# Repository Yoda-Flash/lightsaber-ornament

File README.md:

# lightsaber-ornament
A lightsaber ornament made for Hack Club's Hacky Holidays!

At first, I wanted to make a Yoda ornament PCB, but I realized that it would only look good with green colored lights. Upon further thought, I realized that Lightsabers would look good in nearly any color, which made it perfect as an ornament. Hence, I decided to make this lightsaber ornament PCB, to bring joy to all Star Wars lovers during the holidays!

A simulation of it can be found here: https://wokwi.com/projects/421435412428006401

### 3D Views
#### Front

- 8 Neopixel LEDs, can be set to any color (currently Lightsaber Blue, RGB(46,103,248))
- Piano switch to turn the PCB on and off
- Charger for battery (Only use if the battery is rechargeable!!!)

#### Back

- 4 batteries, which must be CIR2032 form factors

### Schematic

- LEDs, Charger and regulator, Battery, ESP32

### PCB

*Everything made with KiCAD

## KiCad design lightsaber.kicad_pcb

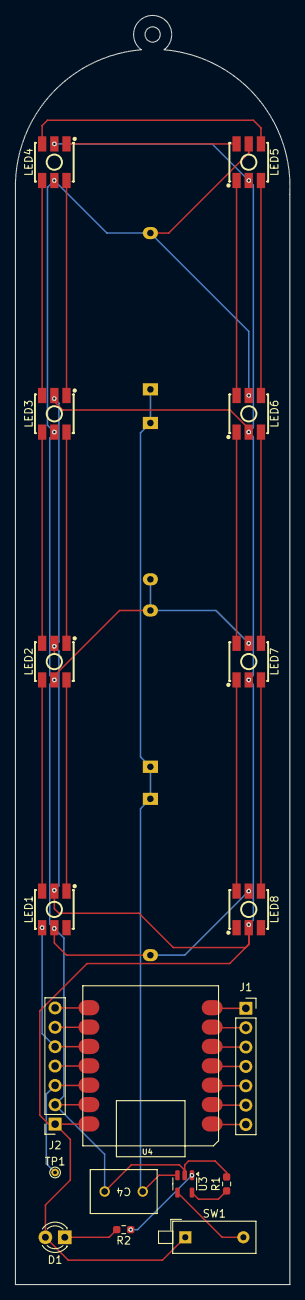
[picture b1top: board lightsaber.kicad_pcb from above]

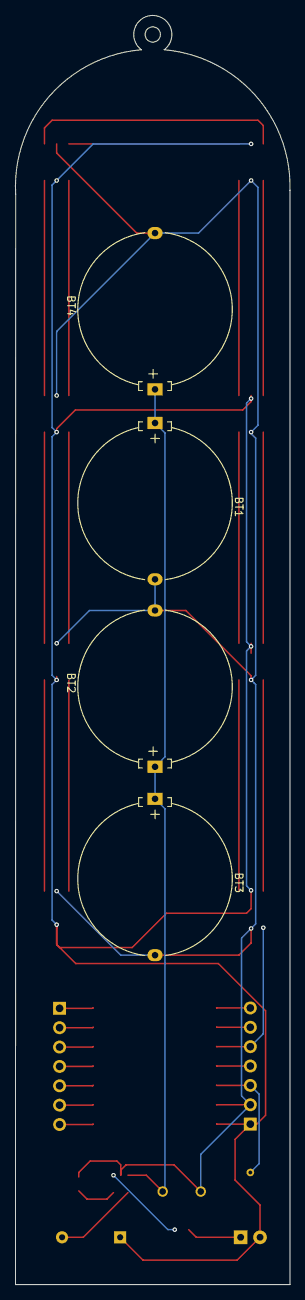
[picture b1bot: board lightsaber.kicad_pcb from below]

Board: 2 copper layers, 36.0 x 166.4 mm, 22 parts (4 on the bottom side), 33 nets.

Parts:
BT1, BT2, BT3, BT4: Battery_Cell; Battery_Panasonic_CR2032-HFN_Horizontal_CircularHoles
C4: 10uF; CAP_FA23_TDK
D1: LED; LED_D3.0mm_Clear
J1, J2: Conn_01x07; PinSocket_1x07_P2.54mm_Vertical
LED1, LED2, LED3, LED4, LED5, LED6, LED7, LED8: WS2813C-V3; LED-SMD_6P-L5.4-W5.0-BR_WS2813C-V3
R1: 33k; R_0603_1608Metric_Pad0.98x0.95mm_HandSolder
R2: 1k; R_0603_1608Metric_Pad0.98x0.95mm_HandSolder
SW1: SW_DIP_x01; SW_DIP_SPSTx01_Piano_10.8x4.1mm_W7.62mm_P2.54mm
TP1: TestPoint; TestPoint_THTPad_D1.0mm_Drill0.5mm
U3: MCP73831-2-OT; SOT-23-5
U4: MOUDLE-SEEEDUINO-XIAO-ESP32C3; MOUDLE14P-SMD-2.54-21X17.8MM

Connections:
+3.3V: J2.3, TP1.1, U4.12 (3V3)
+BATT: BT1.1 (+), BT2.1 (+), BT3.1 (+), BT4.1 (+), C4.1, U3.3 (V_{BAT})
GND: BT1.2 (-), BT2.2 (-), BT3.2 (-), BT4.2 (-), C4.2, J2.2, LED1.5 (GND), LED2.5 (GND), LED3.5 (GND), LED4.5 (GND), LED5.5 (GND), LED6.5 (GND), LED7.5 (GND), LED8.5 (GND), R1.2, U3.2 (V_{SS}), U4.13 (GND)
LED: J2.5, LED1.4 (DIN), U4.10 (PA5_A9_D9_MISO)
unnamed: D1.1 (K), R2.2
unnamed: J1.1, U4.7 (PB08_A6_D6_TX)
unnamed: J1.2, U4.6 (PA9_A5_D5_SCL)
unnamed: J1.3, U4.5 (PA8_A4_D4_SDA)
unnamed: J1.4, U4.4 (PA11_A3_D3)
unnamed: J1.5, U4.3 (PA10_A2_D2)
unnamed: J1.6, U4.2 (PA4_A1_D1)
unnamed: J1.7, U4.1 (PA02_A0_D0)
unnamed: J2.4, U4.11 (PA6_A10_D10_MOSI)
unnamed: J2.6, U4.9 (PA7_A8_D8_SCK)
unnamed: J2.7, U4.8 (PB09_A7_D7_RX)
unnamed: LED1.1 (BO), LED2.6 (BIN)
unnamed: LED1.3 (DO), LED2.4 (DIN)
unnamed: LED2.1 (BO), LED3.6 (BIN)
unnamed: LED2.3 (DO), LED3.4 (DIN)
unnamed: LED3.1 (BO), LED4.6 (BIN)
unnamed: LED3.3 (DO), LED4.4 (DIN)
unnamed: LED4.1 (BO), LED5.6 (BIN)
unnamed: LED4.3 (DO), LED5.4 (DIN)
unnamed: LED5.1 (BO), LED6.6 (BIN)
unnamed: LED5.3 (DO), LED6.4 (DIN)
unnamed: LED6.1 (BO), LED7.6 (BIN)
unnamed: LED6.3 (DO), LED7.4 (DIN)
unnamed: LED7.1 (BO), LED8.6 (BIN)
unnamed: LED7.3 (DO), LED8.4 (DIN)
unnamed: R1.1, U3.5 (PROG)
unnamed: R2.1, U3.1 (STAT)
unnamed: SW1.2, U3.4 (V_{DD})
VBUS: D1.2 (A), J2.1, LED1.2 (VCC), LED2.2 (VCC), LED3.2 (VCC), LED4.2 (VCC), LED5.2 (VCC), LED6.2 (VCC), LED7.2 (VCC), LED8.2 (VCC), SW1.1, U4.14 (5V)
